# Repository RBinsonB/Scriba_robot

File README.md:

# Scriba robot
More information (such as components used, robot building and so on) can be found on the [Hackster page of the project.](https://www.hackster.io/robinb/scriba-robot-a-printing-robot-0048fa).

ROS code has been moved to dedicated repositories.
- [scriba_ros](https://github.com/RBinsonB/scriba_ros): robot base packages (for bringup, motor command, odometry)
- [scriba_localization](https://github.com/RBinsonB/scriba_localization): robot localization related packages (EKF, camera localization)

## Concept
Scriba is a printing robot. It prints on its wake, using the sheet edges and the printing in process as a reference for its navigation. It uses multiple cameras to correct its trajectory and printing alignment through a SLAM algorithm

*Robot concept*

The robot was supposed to be light and portable but grew in sized as the project progressed. It is designed to print on medium and large surfaces.

## Project advancement
WORK IN PROGRESS

Done:
```diff
+ Mechanical Design
+ Electrical Design
+ Components printing/machining
+ Robot assembly
+ PCB assembly
+ ROS serial communication with Arduinos
+ Standard motor command
+ Odometry
+ Odometry and motor command calibration
```
To do:
```diff
- Printhead test
- Low voltage disconnect board
- Step motor command
- Printing command
- Localization by camera
```

### Video: Scriba drive & odometry test

### Video: Scriba front wheel calibration 

## System overview
The detailed [technical design description can be found here.](https://raw.githubusercontent.com/RBinsonB/Scriba_robot/master/Technical_Design_Scriba.pdf)

*Scriba robot bottom view*

*Overall electric & controls diagram*

[The diagram can be found here in higher resolution](https://raw.githubusercontent.com/RBinsonB/Scriba_robot/master/Overall_Electrical_&_Controls_Diagram_Scriba_Robot.pdf)

### Controls
The main computer of the robot is an Odroid-XU4 running Ubuntu 18.04 and mainly relying on a ROS (Robot Operating System) program to run the robot. Computer vision tasks are carried out by OpenCV programs interfaced with the ROS main program.

Actuator control is carried out by two Arduinos Nano, as they can handle real-time operation and GPIO control better than the main computer. They are connected to serial node on the ROS main program.
The robot can be controlled by WiFi from a remote computer by connecting to the Odroid-XU4 via SSH.

### Drive configuration
The robot has a steer drive configuration (also called steerable driving wheel configuration) with one powered and steering wheel at the front and 2 wheel for support at the rear (like a tricycle). This configuration was chosen because of the high driving accuracy it provides when following a navigation path.

*Steer Drive configuration*

### Navigation & Localization system
The robot uses a SLAM algorithm (Simultaneous Localization And Mapping) to navigate. It localize itself by using the printing in process as a reference.

Cameras are located at the front and at the rear of the robot. Their location allows the robot to see the printing in process (with the rear camera) and the previous printing. Being able to see the previous printing after a turn is crucial to correct localization because turns generate a lot of imprecisions in the odometry.

A light source near the camera ensures a correct and uniform lighting of the scanned surface. Inclination of the camera images is corrected by a homographic algorithm.

### Printing system
The printhead is placed on a sweeping system. Both have to stay perpendicular to the printing direction even when the robot is correcting its trajectory. The printing system is therefor able to rotate around the kinematic center of the robot.

*Printing system schematics*

## Code description:
* Arduino: includes Arduino programs.
  * Programs:
    * *Scriba_steering_board_V1*: Program for the arduino of the drive unit. Uses custom message type to receive and execute motor commands, send odometry data and perform calibration operations.
    * *Scriba_steering_board_V2*: Updated version of the firmware to work with potentiometer on the front wheel steer angle.

## Authors

* **Robin Baran** - *Initial work*

## License

This project is licensed under the GNU General Public License version 3

## Acknowledgments

* [Inkjet Printer For the Reprap](https://reprap.org/mediawiki/images/1/1a/Inkjet.pdf) by Amberish Jaipuria
* [DIY Inkjet Printer](https://www.thingiverse.com/thing:8542/) by Patrick Hannan, Jared Knutzen, Nicholas C Lewis, Joy Markham

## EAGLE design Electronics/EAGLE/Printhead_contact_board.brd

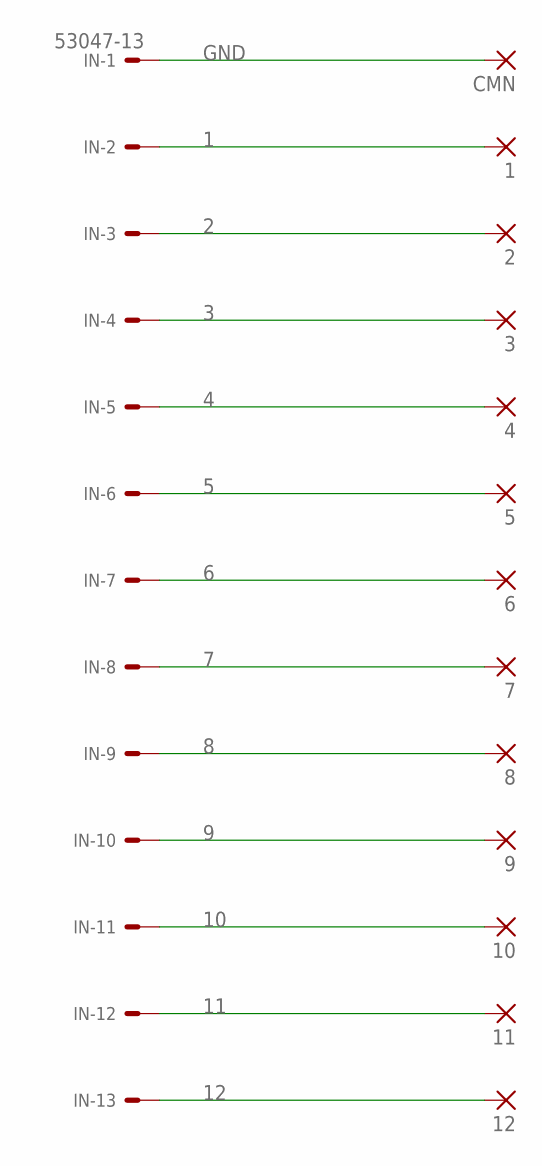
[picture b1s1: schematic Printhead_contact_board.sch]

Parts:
1, 2, 3, 4, 5, 6, 7, 8, 9, 10, 11, 12: SMD2; SMD1,27-2,54
CMN: SMD2; SMD1,27-2,54
IN: 53047-13

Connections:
1: 1.1, IN.2
2: 2.1, IN.3
3: 3.1, IN.4
4: 4.1, IN.5
5: 5.1, IN.6
6: 6.1, IN.7
7: 7.1, IN.8
8: 8.1, IN.9
9: 9.1, IN.10
10: 10.1, IN.11
11: 11.1, IN.12
12: 12.1, IN.13
GND: CMN.1, IN.1

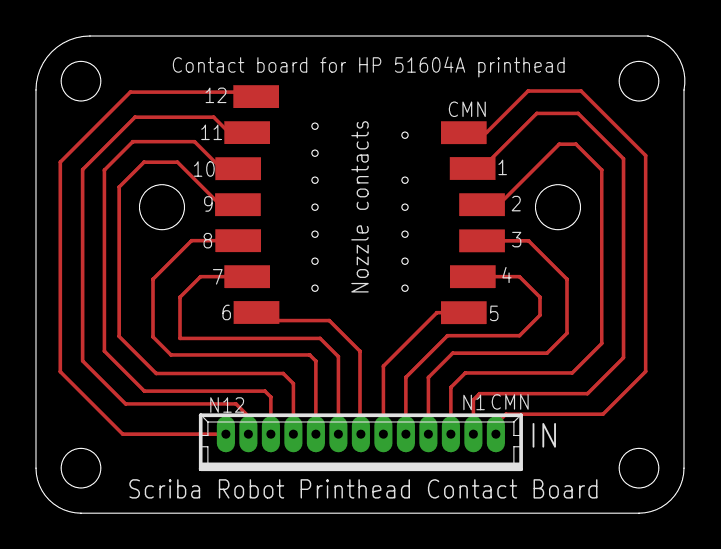
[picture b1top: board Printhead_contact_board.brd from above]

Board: 2 copper layers, 36.0 x 26.5 mm, 14 parts (0 on the bottom side), 13 nets.

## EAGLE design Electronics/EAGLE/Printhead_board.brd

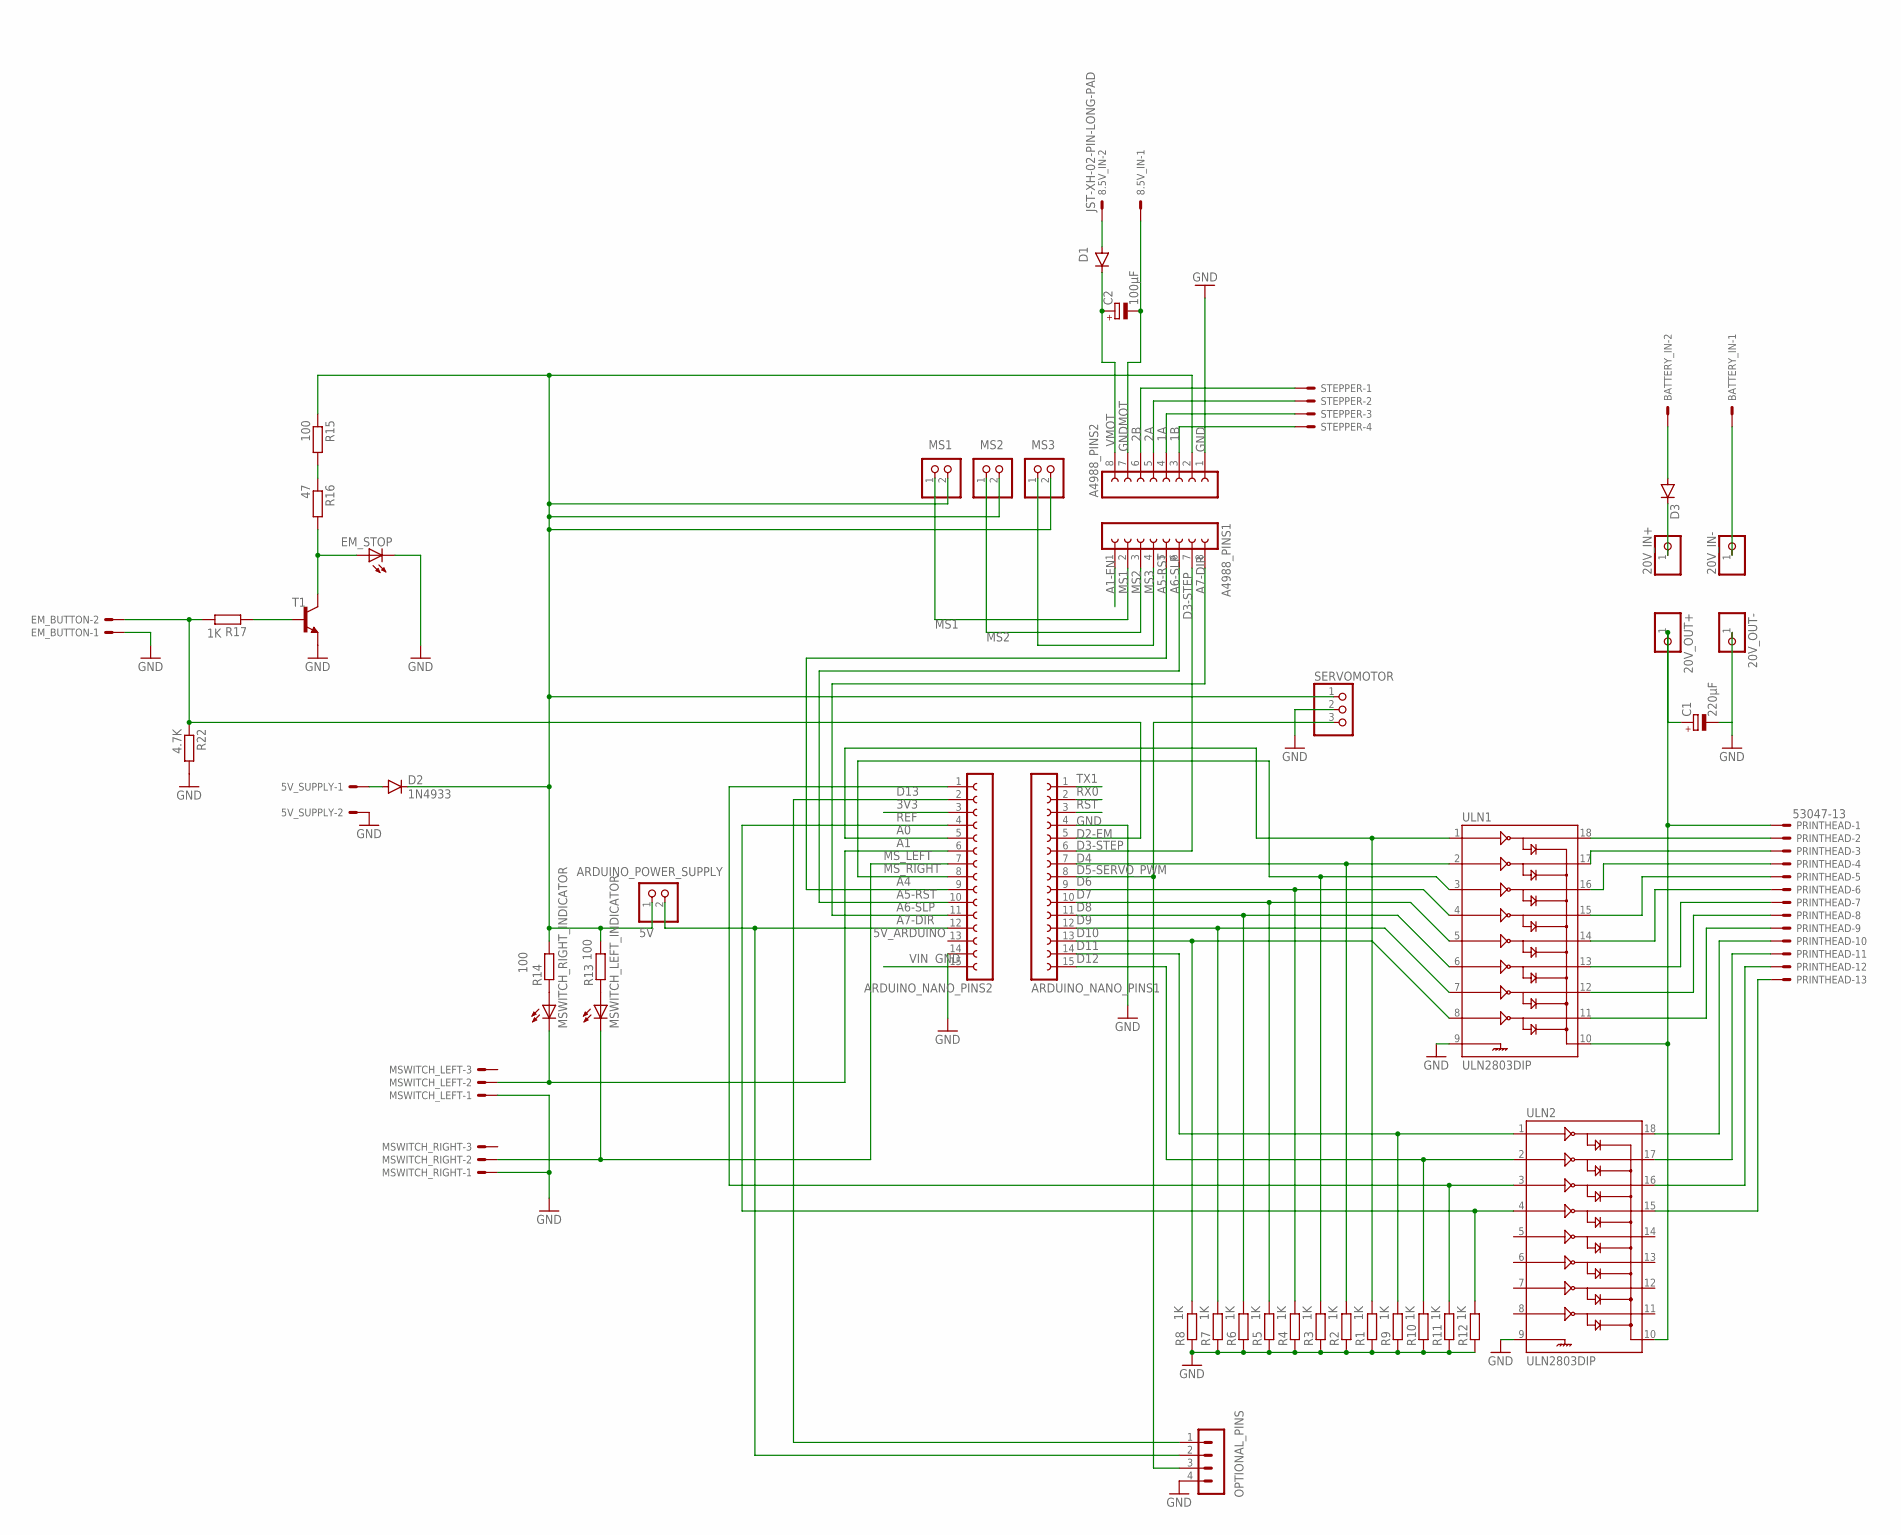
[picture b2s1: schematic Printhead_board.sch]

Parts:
5V_SUPPLY, 8.5V_IN: JST-XH-02-PIN-LONG-PAD; JST-XH-02-PACKAGE-LONG-PAD
20V_IN+, 20V_IN-, 20V_OUT+, 20V_OUT-: PINHD-1X1; 1X01
A4988_PINS1, A4988_PINS2: FE08-1; FE08
ARDUINO_NANO_PINS1, ARDUINO_NANO_PINS2: FE15-1; FE15
ARDUINO_POWER_SUPPLY: PINHD-1X2; 1X02
BATTERY_IN: JST-XH-02-PIN-ROUND-PAD; JST-XH-02-PACKAGE-ROUND-PAD
C1: 220µF; E5-10,5
C2: 100µF; SANYO-OSCON_E
D1: DIODE-DO15-12; DO15-12
D2: 1N4933; DO41-10
D3: DIODE-DO201-15; DO201-15
EM_BUTTON: JST-XH-02-PIN-LONG-PAD; JST-XH-02-PACKAGE-LONG-PAD
EM_STOP: LED5MM
MS1, MS2, MS3: PINHD-1X2; 1X02
MSWITCH_LEFT: JST-XH-03-PIN-LONG-PAD; JST-XH-03-PACKAGE-LONG-PAD
MSWITCH_LEFT_INDICATOR: LED5MM
MSWITCH_RIGHT: JST-XH-03-PIN-LONG-PAD; JST-XH-03-PACKAGE-LONG-PAD
MSWITCH_RIGHT_INDICATOR: LED5MM
OPTIONAL_PINS: MA04-1
PRINTHEAD: 53047-13
R1, R2, R3, R4, R5, R6, R7, R8, R9, R10, R11, R12, R17: 1K; 0207/7
R13, R14, R15: 100; 0207/7
R16: 47; 0207/7
R22: 4.7K; 0207/7
SERVOMOTOR: PINHD-1X3; 1X03
STEPPER: JST-XH-04-PIN-LONG-PAD; JST-XH-04-PACKAGE-LONG-PAD
T1: 2N2222; TO92-EBC-OVAL
ULN1, ULN2: ULN2803DIP; DIL18

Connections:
1A: A4988_PINS2.4, STEPPER.3
1B: A4988_PINS2.3, STEPPER.4
2A: A4988_PINS2.5, STEPPER.2
2B: A4988_PINS2.6, STEPPER.1
3V3: ARDUINO_NANO_PINS2.2, OPTIONAL_PINS.1
5V: A4988_PINS2.2, ARDUINO_POWER_SUPPLY.1, D2.C, MS1.2, MS2.2, MS3.2, R13.2, R14.2, R15.1, SERVOMOTOR.1
5V_ARDUINO: ARDUINO_NANO_PINS2.12, ARDUINO_POWER_SUPPLY.2, OPTIONAL_PINS.2
A0: ARDUINO_NANO_PINS2.4, R12.2, ULN2.4
A1: ARDUINO_NANO_PINS2.5, R1.2, ULN1.1
A1-EN: A4988_PINS1.1
A4: ARDUINO_NANO_PINS2.8, R3.2, ULN1.3
A5-RST: A4988_PINS1.5, ARDUINO_NANO_PINS2.9
A6-SLP: A4988_PINS1.6, ARDUINO_NANO_PINS2.10
A7-DIR: A4988_PINS1.8, ARDUINO_NANO_PINS2.11
D2-EM: ARDUINO_NANO_PINS1.5, EM_BUTTON.2, R17.2, R22.1
D3-STEP: A4988_PINS1.7, ARDUINO_NANO_PINS1.6
D4: ARDUINO_NANO_PINS1.7, R2.2, ULN1.2
D5-SERVO_PWM: ARDUINO_NANO_PINS1.8, OPTIONAL_PINS.3, SERVOMOTOR.3
D6: ARDUINO_NANO_PINS1.9, R4.2, ULN1.4
D7: ARDUINO_NANO_PINS1.10, R5.2, ULN1.5
D8: ARDUINO_NANO_PINS1.11, R6.2, ULN1.6
D9: ARDUINO_NANO_PINS1.12, R7.2, ULN1.7
D10: ARDUINO_NANO_PINS1.13, R8.2, ULN1.8
D11: ARDUINO_NANO_PINS1.14, R9.2, ULN2.1
D12: ARDUINO_NANO_PINS1.15, R10.2, ULN2.2
D13: ARDUINO_NANO_PINS2.1, R11.2, ULN2.3
GND: 5V_SUPPLY.2, 20V_OUT-.1, A4988_PINS2.1, ARDUINO_NANO_PINS1.4, ARDUINO_NANO_PINS2.14, C1.-, EM_BUTTON.1, EM_STOP.K (C), MSWITCH_LEFT.1, MSWITCH_RIGHT.1, OPTIONAL_PINS.4, R1.1, R2.1, R3.1, R4.1, R5.1, R6.1, R7.1, R8.1, R9.1, R10.1, R11.1, R12.1, R22.2, SERVOMOTOR.2, T1.E, ULN1.9, ULN2.9
GNDMOT: 8.5V_IN.1, A4988_PINS2.7, C2.-
MS1: A4988_PINS1.2, MS1.1
MS2: A4988_PINS1.3, MS2.1
MS3: A4988_PINS1.4, MS3.1
MS_LEFT: ARDUINO_NANO_PINS2.6, MSWITCH_LEFT.2, MSWITCH_RIGHT_INDICATOR.K (C)
MS_RIGHT: ARDUINO_NANO_PINS2.7, MSWITCH_LEFT_INDICATOR.K (C), MSWITCH_RIGHT.2
N1: PRINTHEAD.2, ULN1.18
N12: PRINTHEAD.13, ULN2.15
unnamed: EM_STOP.A, R16.2, T1.C
unnamed: R17.1, T1.B
unnamed: R15.2, R16.1
unnamed: BATTERY_IN.2, D3.A
unnamed: 5V_SUPPLY.1, D2.A
unnamed: PRINTHEAD.3, ULN1.17
unnamed: PRINTHEAD.4, ULN1.16
unnamed: PRINTHEAD.5, ULN1.15
unnamed: PRINTHEAD.6, ULN1.14
unnamed: PRINTHEAD.7, ULN1.13
unnamed: PRINTHEAD.8, ULN1.12
unnamed: PRINTHEAD.9, ULN1.11
unnamed: PRINTHEAD.10, ULN2.18
unnamed: PRINTHEAD.11, ULN2.17
unnamed: PRINTHEAD.12, ULN2.16
unnamed: 8.5V_IN.2, D1.A
unnamed: MSWITCH_LEFT_INDICATOR.A, R13.1
unnamed: MSWITCH_RIGHT_INDICATOR.A, R14.1
unnamed: 20V_IN-.1, BATTERY_IN.1
unnamed: 20V_OUT+.1, C1.+, PRINTHEAD.1, ULN1.10, ULN2.10
unnamed: 20V_IN+.1, D3.C
REF: ARDUINO_NANO_PINS2.3
RST: ARDUINO_NANO_PINS1.3
RX0: ARDUINO_NANO_PINS1.2
TX1: ARDUINO_NANO_PINS1.1
VIN: ARDUINO_NANO_PINS2.15
VMOT: A4988_PINS2.8, C2.+, D1.C

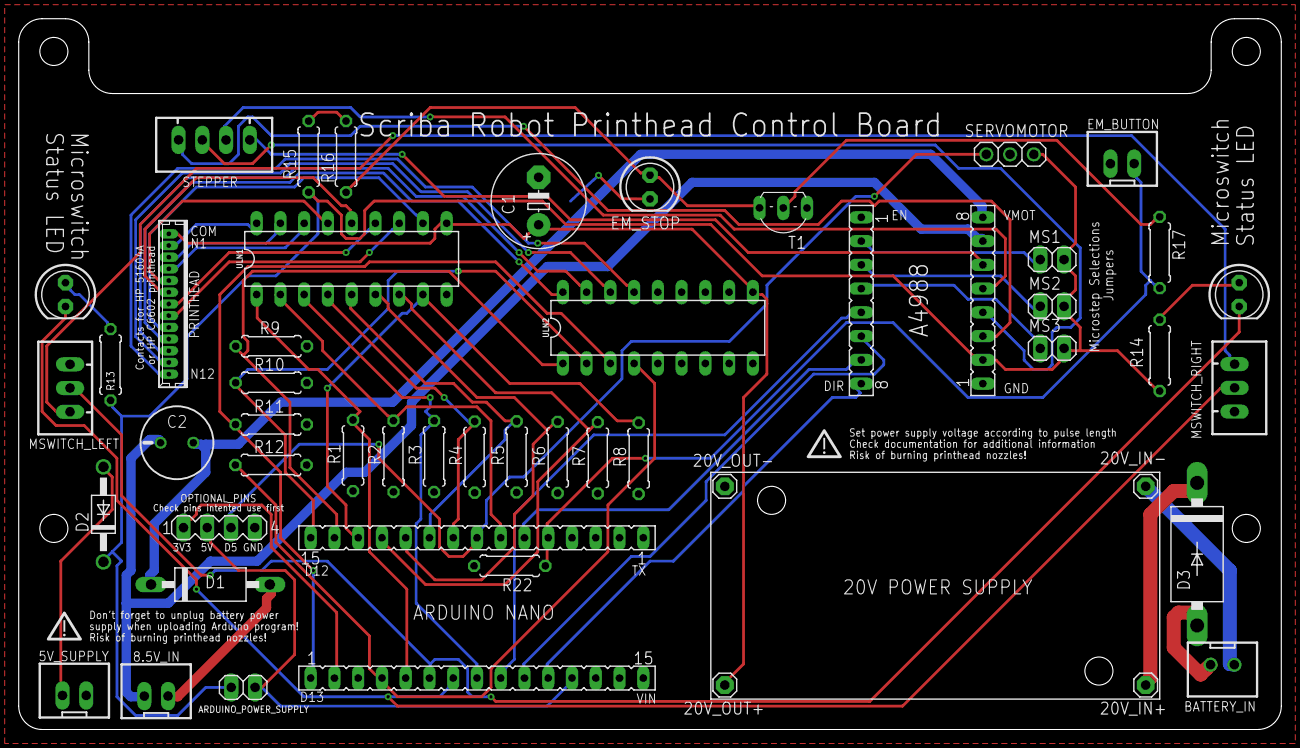
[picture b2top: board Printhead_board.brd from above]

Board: 2 copper layers, 135.0 x 76.0 mm, 51 parts (0 on the bottom side), 56 nets.

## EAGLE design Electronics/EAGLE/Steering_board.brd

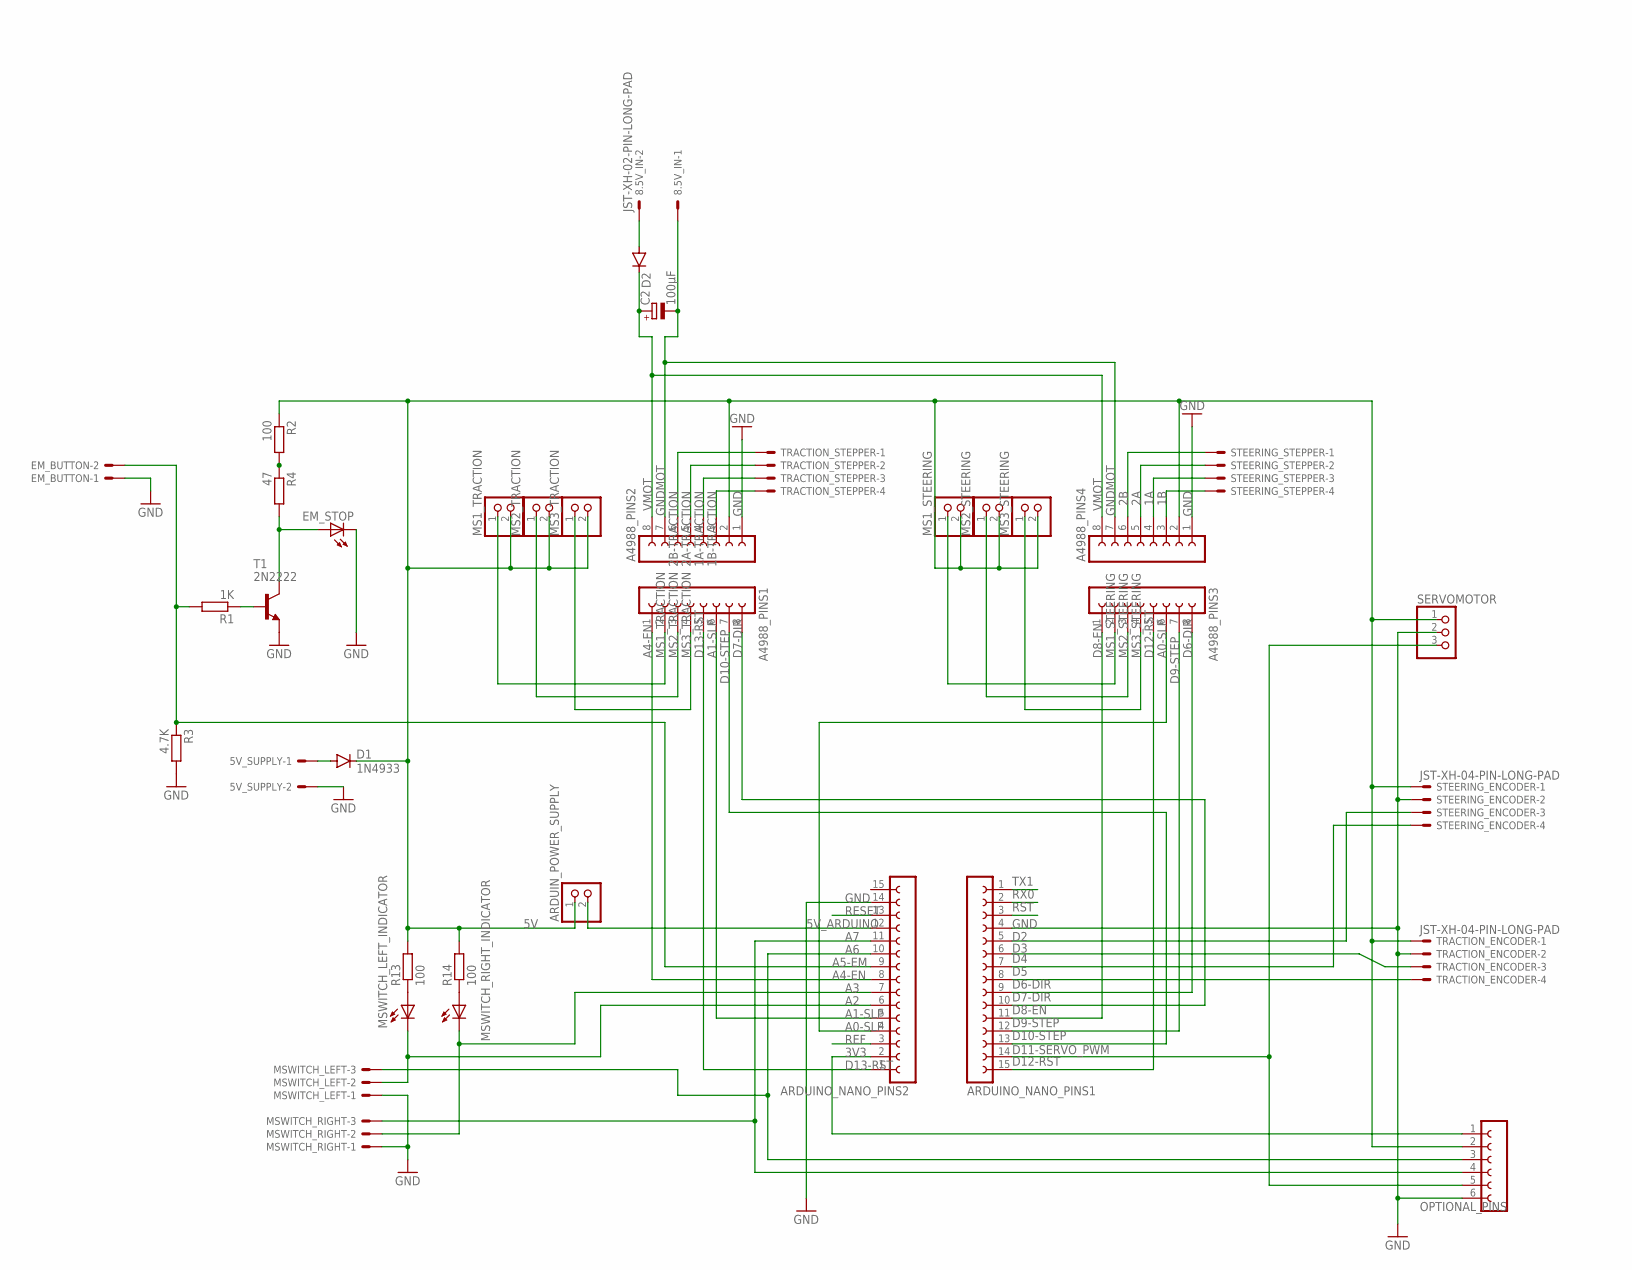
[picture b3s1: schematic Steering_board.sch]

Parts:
5V_SUPPLY, 8.5V_IN: JST-XH-02-PIN-LONG-PAD; JST-XH-02-PACKAGE-LONG-PAD
A4988_PINS1, A4988_PINS2, A4988_PINS3, A4988_PINS4: FE08-1; FE08
ARDUINO_NANO_PINS1, ARDUINO_NANO_PINS2: FE15-1; FE15
ARDUIN_POWER_SUPPLY: PINHD-1X2; 1X02
C2: 100µF; SANYO-OSCON_E
D1: 1N4933; DO41-10
D2: DIODE-DO15-12; DO15-12
EM_BUTTON: JST-XH-02-PIN-LONG-PAD; JST-XH-02-PACKAGE-LONG-PAD
EM_STOP: LED5MM
MS1_STEERING, MS1_TRACTION, MS2_STEERING, MS2_TRACTION, MS3_STEERING, MS3_TRACTION: PINHD-1X2; 1X02
MSWITCH_LEFT: JST-XH-03-PIN-LONG-PAD; JST-XH-03-PACKAGE-LONG-PAD
MSWITCH_LEFT_INDICATOR: LED5MM
MSWITCH_RIGHT: JST-XH-03-PIN-LONG-PAD; JST-XH-03-PACKAGE-LONG-PAD
MSWITCH_RIGHT_INDICATOR: LED5MM
OPTIONAL_PINS: FE06-1; FE06
R1: 1K; 0207/7
R2, R13, R14: 100; 0207/7
R3: 4.7K; 0207/7
R4: 47; 0207/7
SERVOMOTOR: PINHD-1X3; 1X03
STEERING_ENCODER: JST-XH-04-PIN-LONG-PAD; JST-XH-04-PACKAGE-LONG-PAD
STEERING_STEPPER: JST-XH-04-PIN-LONG-PAD; JST-XH-04-PACKAGE-LONG-PAD
T1: 2N2222; TO92-EBC-OVAL
TRACTION_ENCODER: JST-XH-04-PIN-LONG-PAD; JST-XH-04-PACKAGE-LONG-PAD
TRACTION_STEPPER: JST-XH-04-PIN-LONG-PAD; JST-XH-04-PACKAGE-LONG-PAD

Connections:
1A: A4988_PINS4.4, STEERING_STEPPER.3
1A-TRACTION: A4988_PINS2.4, TRACTION_STEPPER.3
1B: A4988_PINS4.3, STEERING_STEPPER.4
1B-TRACTION: A4988_PINS2.3, TRACTION_STEPPER.4
2A: A4988_PINS4.5, STEERING_STEPPER.2
2A-TRACTION: A4988_PINS2.5, TRACTION_STEPPER.2
2B: A4988_PINS4.6, STEERING_STEPPER.1
2B-TRACTION: A4988_PINS2.6, TRACTION_STEPPER.1
3V3: ARDUINO_NANO_PINS2.2, OPTIONAL_PINS.1
5V: A4988_PINS2.2, A4988_PINS4.2, ARDUIN_POWER_SUPPLY.1, D1.C, MS1_STEERING.2, MS1_TRACTION.2, MS2_STEERING.2, MS2_TRACTION.2, MS3_STEERING.2, MS3_TRACTION.2, OPTIONAL_PINS.2, R2.1, R13.2, R14.2, SERVOMOTOR.1, STEERING_ENCODER.1, TRACTION_ENCODER.1
5V_ARDUINO: ARDUINO_NANO_PINS2.12, ARDUIN_POWER_SUPPLY.2
A0-SLP: A4988_PINS3.6, ARDUINO_NANO_PINS2.4
A1-SLP: A4988_PINS1.6, ARDUINO_NANO_PINS2.5
A2: ARDUINO_NANO_PINS2.6, MSWITCH_LEFT.2, MSWITCH_LEFT_INDICATOR.K (C)
A3: ARDUINO_NANO_PINS2.7, MSWITCH_RIGHT.2, MSWITCH_RIGHT_INDICATOR.K (C)
A4-EN: A4988_PINS1.1, ARDUINO_NANO_PINS2.8
A5-EM: ARDUINO_NANO_PINS2.9, EM_BUTTON.2, R1.2, R3.1
A6: ARDUINO_NANO_PINS2.10, MSWITCH_LEFT.3, OPTIONAL_PINS.3
A7: ARDUINO_NANO_PINS2.11, MSWITCH_RIGHT.3, OPTIONAL_PINS.4
D2: ARDUINO_NANO_PINS1.5, STEERING_ENCODER.3
D3: ARDUINO_NANO_PINS1.6, TRACTION_ENCODER.3
D4: ARDUINO_NANO_PINS1.7, STEERING_ENCODER.4
D5: ARDUINO_NANO_PINS1.8, TRACTION_ENCODER.4
D6-DIR: A4988_PINS3.8, ARDUINO_NANO_PINS1.9
D7-DIR: A4988_PINS1.8, ARDUINO_NANO_PINS1.10
D8-EN: A4988_PINS3.1, ARDUINO_NANO_PINS1.11
D9-STEP: A4988_PINS3.7, ARDUINO_NANO_PINS1.12
D10-STEP: A4988_PINS1.7, ARDUINO_NANO_PINS1.13
D11-SERVO_PWM: ARDUINO_NANO_PINS1.14, OPTIONAL_PINS.5, SERVOMOTOR.3
D12-RST: A4988_PINS3.5, ARDUINO_NANO_PINS1.15
D13-RST: A4988_PINS1.5, ARDUINO_NANO_PINS2.1
GND: 5V_SUPPLY.2, A4988_PINS2.1, A4988_PINS4.1, ARDUINO_NANO_PINS1.4, ARDUINO_NANO_PINS2.14, EM_BUTTON.1, EM_STOP.K (C), MSWITCH_LEFT.1, MSWITCH_RIGHT.1, OPTIONAL_PINS.6, R3.2, SERVOMOTOR.2, STEERING_ENCODER.2, T1.E, TRACTION_ENCODER.2
GNDMOT: 8.5V_IN.1, A4988_PINS2.7, A4988_PINS4.7, C2.-
MS1_STEERING: A4988_PINS3.2, MS1_STEERING.1
MS1_TRACTION: A4988_PINS1.2, MS1_TRACTION.1
MS2_STEERING: A4988_PINS3.3, MS2_STEERING.1
MS2_TRACTION: A4988_PINS1.3, MS2_TRACTION.1
MS3_STEERING: A4988_PINS3.4, MS3_STEERING.1
MS3_TRACTION: A4988_PINS1.4, MS3_TRACTION.1
unnamed: 8.5V_IN.2, D2.A
unnamed: 5V_SUPPLY.1, D1.A
unnamed: R2.2, R4.1
unnamed: EM_STOP.A, R4.2, T1.C
unnamed: R1.1, T1.B
unnamed: MSWITCH_LEFT_INDICATOR.A, R13.1
unnamed: MSWITCH_RIGHT_INDICATOR.A, R14.1
REF: ARDUINO_NANO_PINS2.3
RESET: ARDUINO_NANO_PINS2.13
RST: ARDUINO_NANO_PINS1.3
RX0: ARDUINO_NANO_PINS1.2
TX1: ARDUINO_NANO_PINS1.1
VMOT: A4988_PINS2.8, A4988_PINS4.8, C2.+, D2.C

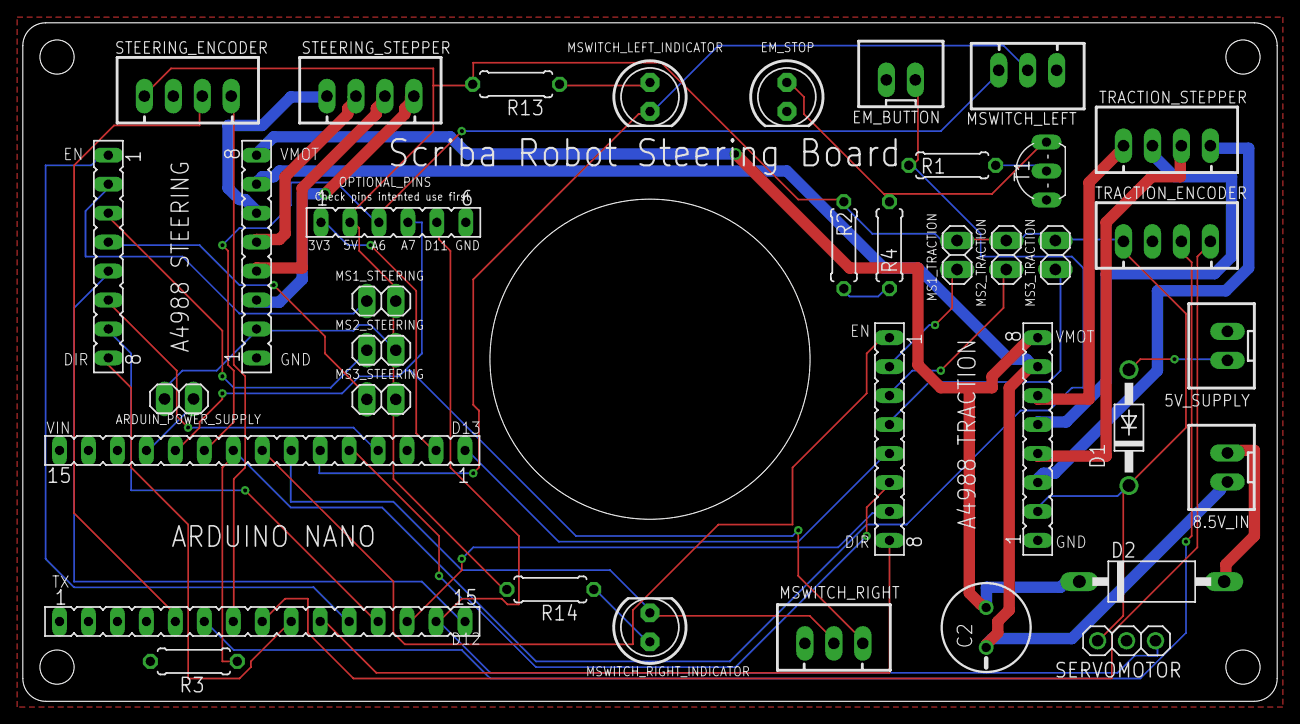
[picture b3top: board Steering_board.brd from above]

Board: 2 copper layers, 110.0 x 59.5 mm, 37 parts (0 on the bottom side), 47 nets.

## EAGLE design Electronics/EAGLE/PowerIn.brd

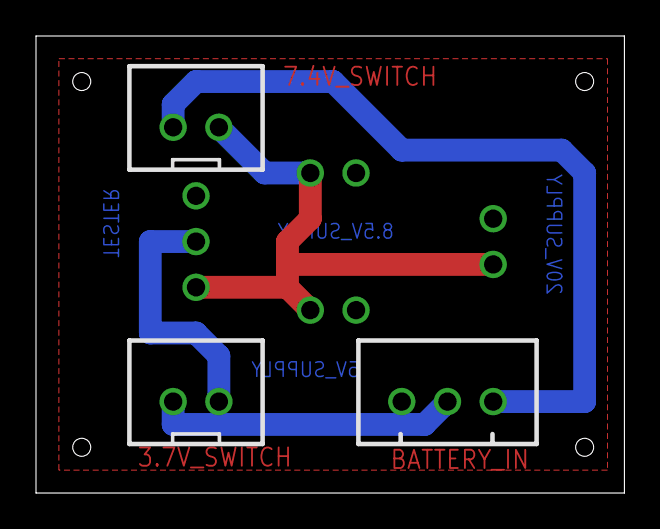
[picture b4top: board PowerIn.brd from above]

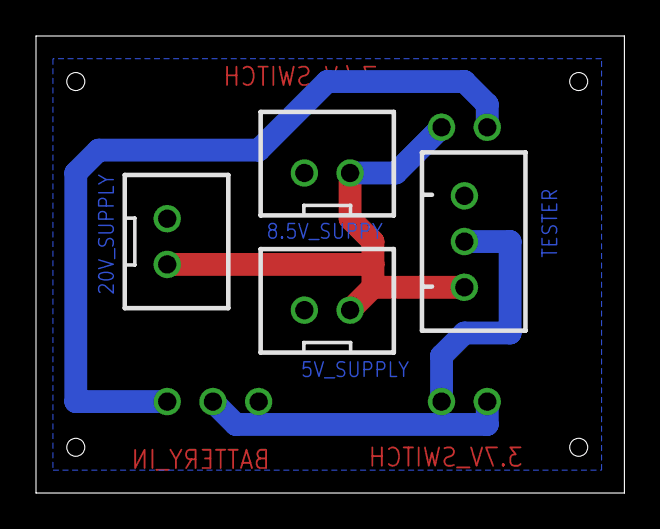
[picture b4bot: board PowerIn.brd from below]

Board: 2 copper layers, 32.7 x 25.4 mm, 7 parts (4 on the bottom side), 5 nets.

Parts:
3.7V_SWITCH, 5V_SUPPLY, 7.4V_SWITCH, 8.5V_SUPPY, 20V_SUPPLY: JST-XH-02-PIN-ROUND-PAD; JST-XH-02-PACKAGE-ROUND-PAD
BATTERY_IN: JST-XH-03-PIN-ROUND-PAD; JST-XH-03-PACKAGE-ROUND-PAD
TESTER: JST-XH-03-PIN-ROUND-PAD; JST-XH-03-PACKAGE-ROUND-PAD

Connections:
GND: 5V_SUPPLY.1, 8.5V_SUPPY.1, 20V_SUPPLY.1, BATTERY_IN.1, TESTER.1
unnamed: 7.4V_SWITCH.1, BATTERY_IN.3
unnamed: 3.7V_SWITCH.1, BATTERY_IN.2
unnamed: 3.7V_SWITCH.2, TESTER.2
unnamed: 5V_SUPPLY.2, 7.4V_SWITCH.2, 8.5V_SUPPY.2, 20V_SUPPLY.2, TESTER.3

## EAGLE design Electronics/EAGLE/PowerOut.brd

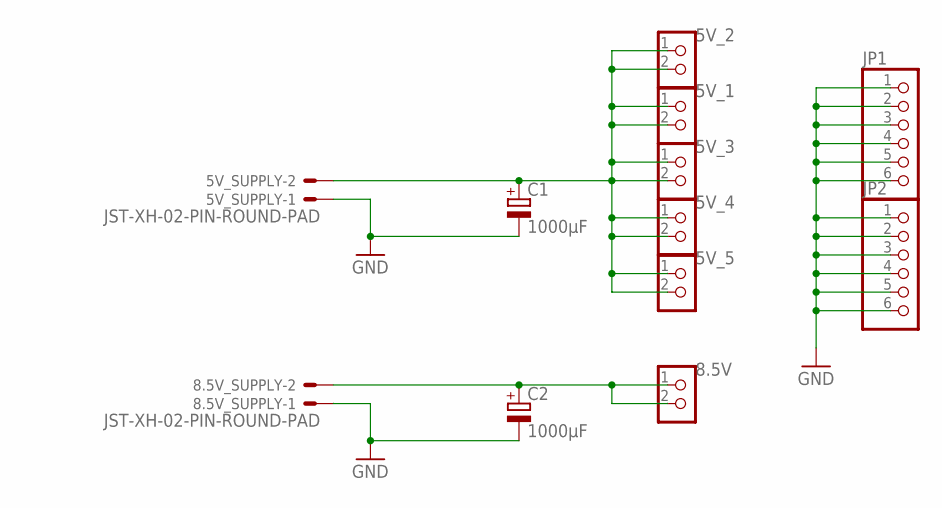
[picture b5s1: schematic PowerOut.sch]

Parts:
5V_1, 5V_2, 5V_3, 5V_4, 5V_5, 8.5V: CON_TERMINAL_BLOCK_02-5MM; TERMINAL_BLOCK_2P_5
5V_SUPPLY, 8.5V_SUPPLY: JST-XH-02-PIN-ROUND-PAD; JST-XH-02-PACKAGE-ROUND-PAD
C1, C2: 1000µF; E5-10,5
JP1, JP2: PINHD-1X6; 1X06

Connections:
GND: 5V_SUPPLY.1, 8.5V_SUPPLY.1, C1.-, C2.-, JP1.1, JP1.2, JP1.3, JP1.4, JP1.5, JP1.6, JP2.1, JP2.2, JP2.3, JP2.4, JP2.5, JP2.6
unnamed: 5V_1.1, 5V_1.2, 5V_2.1, 5V_2.2, 5V_3.1, 5V_3.2, 5V_4.1, 5V_4.2, 5V_5.1, 5V_5.2, 5V_SUPPLY.2, C1.+
unnamed: 8.5V.1, 8.5V.2, 8.5V_SUPPLY.2, C2.+

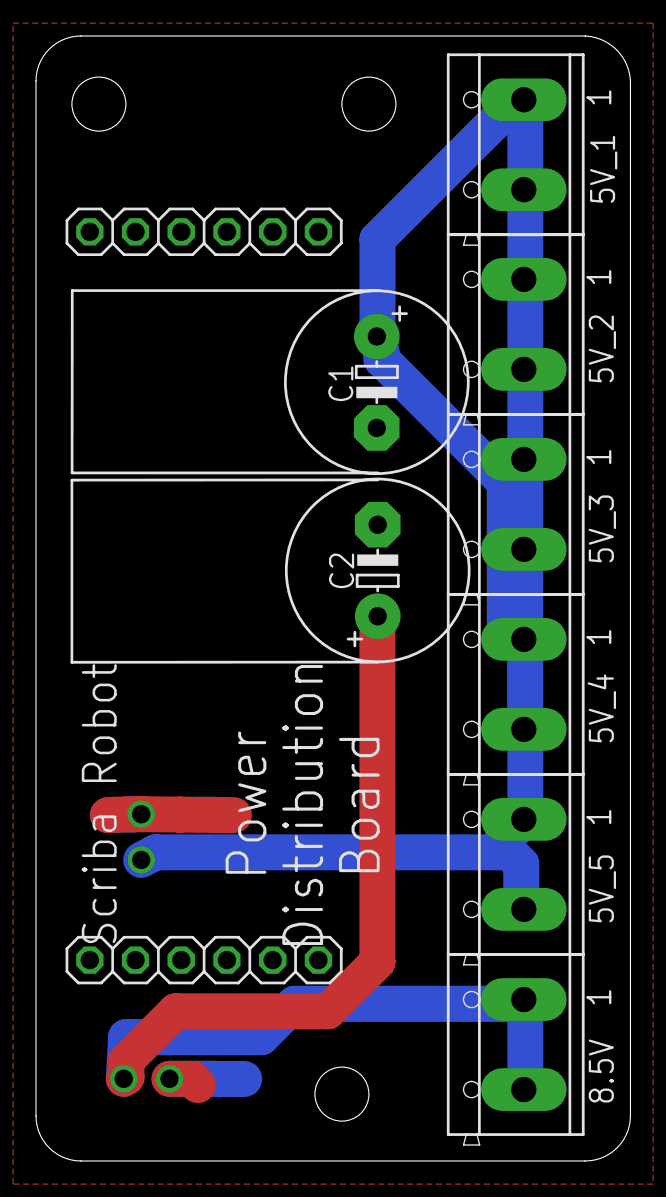
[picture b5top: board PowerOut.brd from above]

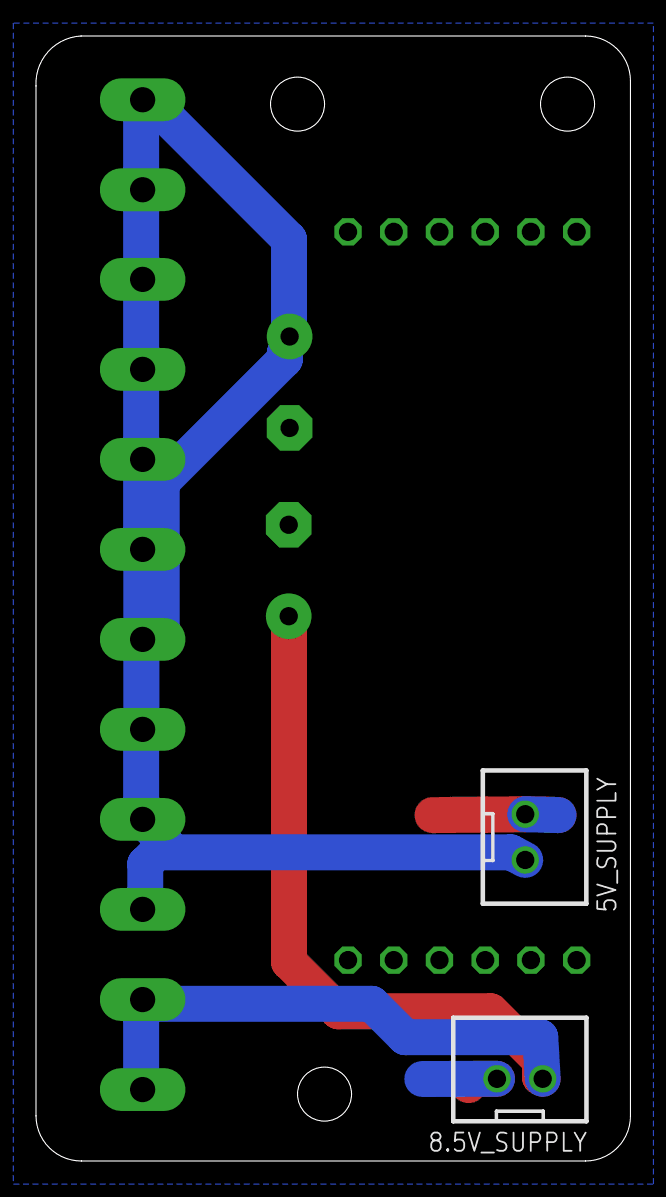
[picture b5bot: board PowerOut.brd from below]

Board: 2 copper layers, 33.0 x 62.5 mm, 12 parts (2 on the bottom side), 3 nets.

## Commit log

2019-09-04 Minor changes
2019-09-04 Minor changes & spell check
2019-09-30 Folders reorganized
2021-02-11 Add potentiometer data to odom data message
2021-02-11 Add angle kalman filter library
2021-02-11 Add steering angle potentiometer in arduino firmware
2021-02-14 Add angle kalman filter in odometry broadcaster
2021-02-16 Refactor odometry broadcaster code and add params
2021-02-26 Add steering potentiometer and comments to message files
2021-02-26 Rename variables to follow message definition changes
2021-02-26 Reinsert steering board firmware V2 as independant folder
2021-02-27 Change variable name after message definition update
2021-06-08 Add new Arduino firmware
2021-06-08 Move ROS code to dedicated repo
2021-10-26 Add steering potentiometer to CAD
2021-10-26 Add calibration rig
2021-10-26 Add missing CAD updates after adding steering potentiometer
